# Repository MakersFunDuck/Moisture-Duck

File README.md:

# Moisture-Duck
ATtiny13A Resistive Soil Sensor for Duck Lovers

Moisture-Duck helps you keep track of your plants' soil moisture and alerts you if they need watering. It utilizes the resistance measurement technique to gauge soil moisture levels. Two probes, in combination with the substrate, constitute a variable resistor. Greater soil moisture translates to improved conductivity and decreased electrical resistance. With the addition of a 12k fixed resistor, the system creates a voltage divider. The microcontroller's ADC measures this voltage. The design is inspired by the SparkFun Soil Moisture Sensor.

Description:
------------
The Moisture Duck is a device that measures soil moisture and emits an acoustic and optical signal if the soil is too dry. The device is based on ATtiny13, which spends most of its time in sleep mode and wakes up every eight seconds to take measurements. It can also be activated by pressing the TEST button, and the correct threshold value can be set by turning the potentiometer. To calibrate the device, it should be placed in dry soil and the potentiometer should be adjusted until the alarm is triggered. The device is compiled using MicroCore and default settings should be left unchanged. Arduino core functions and libraries are not used, and the makefile can be used for compilation without Arduino IDE. The fuse settings are -U lfuse:w:0x3b:m -U hfuse:w:0xff:m.

Compiling and Uploading:
------------

You can program the ATtiny either before soldering using an SOP adapter, or after soldering using ICSP pins. The AVR Programmer Adapter can help with this.
If using the Arduino IDE

    Make sure you have installed MicroCore.
    Go to Tools -> Board -> MicroCore and select ATtiny13.
    Go to Tools and choose the following board options:
        Clock: 128 kHz internal osc.
        BOD: BOD disabled
        Timing: Micros disabled
    Connect your programmer to your PC and to the ATtiny.
    Go to Tools -> Programmer and select your ISP programmer (e.g. USBasp).
    Go to Tools -> Burn Bootloader to burn the fuses.
    Open main.ino and click Upload.

If using the precompiled hex-file

    Make sure you have installed avrdude.
    Connect your programmer to your PC and to the ATtiny.
    Open a terminal.
    Navigate to the folder with the hex-file.
    Execute the following command (if necessary replace "usbasp" with the programmer you use):

    avrdude -c usbasp -p t13 -U lfuse:w:0x3b:m -U hfuse:w:0xff:m -U flash:w:main.hex

If using the makefile (Linux/Mac)

    Make sure you have installed avr-gcc toolchain and avrdude.
    Connect your programmer to your PC and to the ATtiny.
    Open a terminal.
    Navigate to the folder with the makefile and sketch.
    Run PROGRMR=usbasp make install to compile, burn the fuses and upload the firmware (change PROGRMR accordingly).

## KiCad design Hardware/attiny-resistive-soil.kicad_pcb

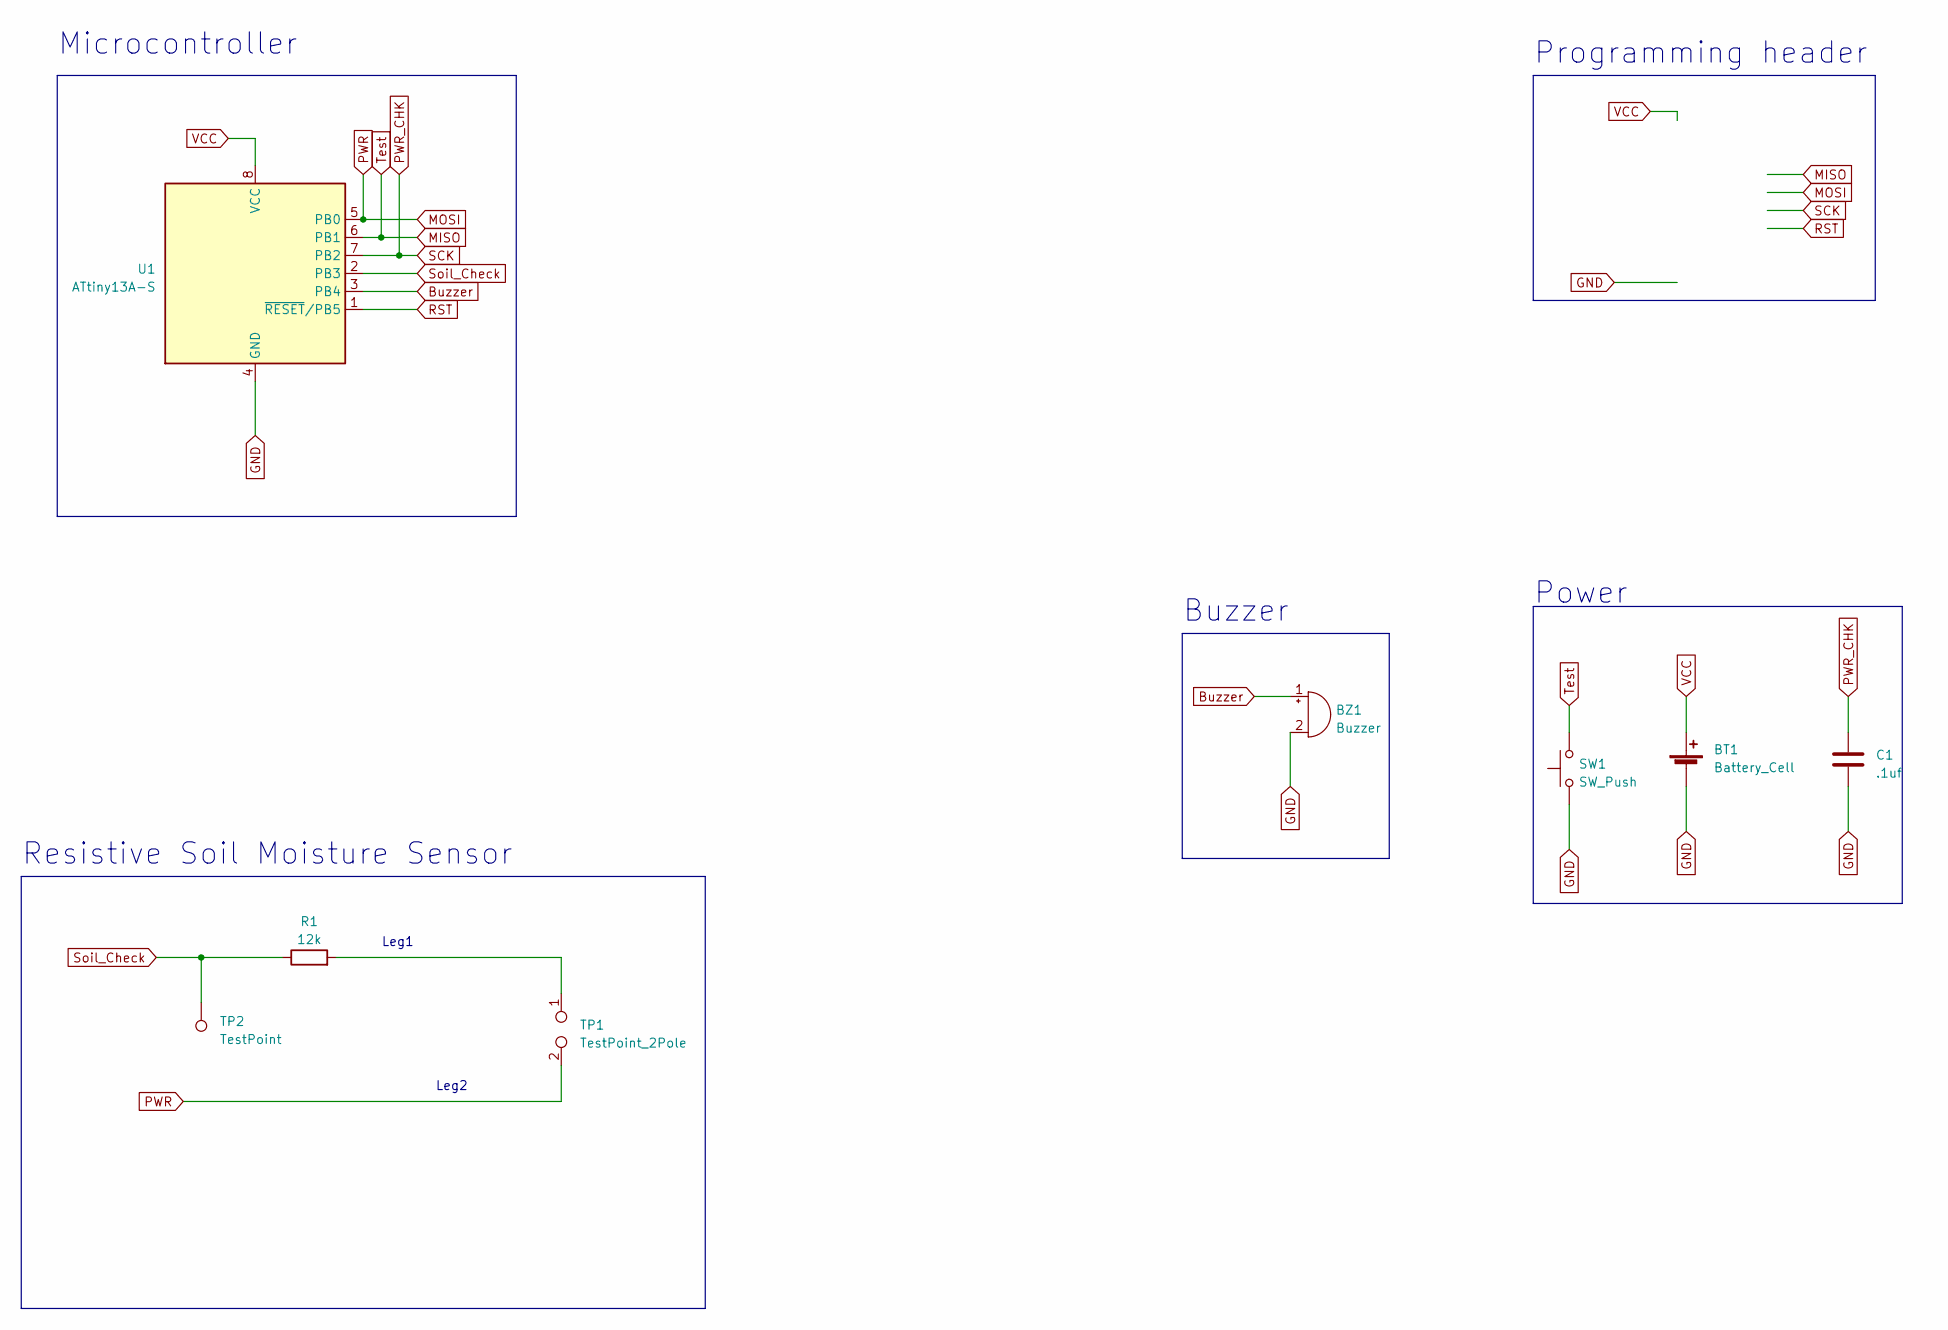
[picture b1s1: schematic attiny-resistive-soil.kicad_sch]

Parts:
BT1: Battery_Cell; BatteryHolder_Keystone_1060_1x2032
BZ1: Buzzer; MagneticBuzzer_CUI_CMT-8504-100-SMT
C1: .1uf; C_0805_2012Metric_Pad1.18x1.45mm_HandSolder
R1: 12k; R_0805_2012Metric_Pad1.20x1.40mm_HandSolder
SW1: SW_Push; SW_SPST_CK_RS282G05A3
TP1: TestPoint_2Pole; PinSocket_1x02_P2.54mm_Vertical
TP2: TestPoint; Pin_D1.4mm_L8.5mm_W2.8mm_FlatFork
U1: ATtiny13A-S; SOIC-8W_5.3x5.3mm_P1.27mm

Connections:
Buzzer: BZ1.1 (-), U1.3 (PB4)
GND: BT1.2 (-), BZ1.2 (+), C1.2, SW1.1, U1.4 (GND)
MISO: SW1.2, U1.6 (PB1)
MOSI: TP1.2, U1.5 (PB0)
unnamed: R1.2, TP1.1
PWR_CHK: C1.1, U1.7 (PB2)
RST: U1.1 (~RESET/PB5)
Soil_Check: R1.1, TP2.1, U1.2 (PB3)
VCC: BT1.1 (+), U1.8 (VCC)

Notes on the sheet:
Buzzer
Resistive Soil Moisture Sensor
Leg1
Programming header
Leg2
Microcontroller
Power

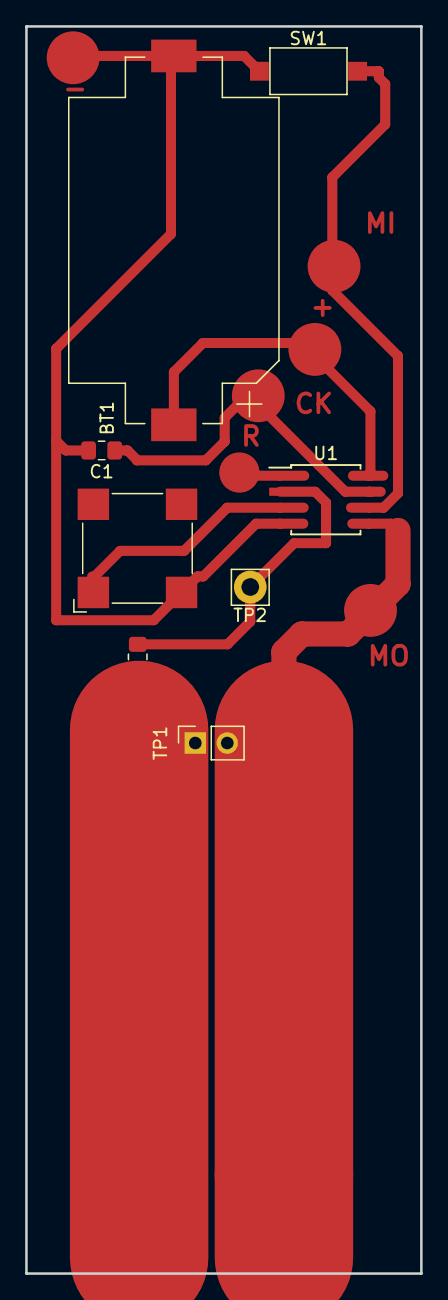
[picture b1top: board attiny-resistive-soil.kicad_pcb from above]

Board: 2 copper layers, 31.4 x 99.1 mm, 8 parts (0 on the bottom side), 8 nets.

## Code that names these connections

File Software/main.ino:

// ===================================================================================
// Project:   Moisture-Duck - Soil Moisture Monitor based on ATtiny13A
// Version:   v1.0
// Year:      2023
// Github:    https://github.com/MakersFunDuck
// Youtube:   https://www.youtube.com/@makersfunduck
// License:   GNU General Public License v3.0
// ===================================================================================
//
// Description:
// ------------
// The ATtiny13 is programmed to enter sleep mode for most of the time.
// It utilizes the watchdog timer to wake up every 2 minutes and measure soil moisture,
// comparing it to a preset threshold value.
// If the soil is too dry, it triggers a brief acoustic signal from the buzzer before going back to sleep mode.
//
// Additionally, the Moisture-Duck can also be activated by pressing the TEST button. (pin
// change interrupt).  It outputs an acoustic signal to indicate if the battery power is sufficient,
// followed by measurements of soil moisture until the button is released.

//
// To calibrate the Moisture-Duck, it should be placed in slightly dry soil,
// Then voltage 
//
// Wiring:
// -------
//                                +-\/-+
//   		   --- RST ADC0 PB5  1|°   |8  Vcc
//  Soil_Check ------- ADC3 PB3  2|    |7  PB2 ADC1 -------- PWR_CHK
// 	BUZZER ----------- ADC2 PB4  3|    |6  PB1 AIN1 OC0B --- TEST
//                          GND  4|    |5  PB0 AIN0 OC0A --- PWR
//                                +----+
//
// Compilation Settings:
// ---------------------
// Controller:  ATtiny13A
// Core:        MicroCore (https://github.com/MCUdude/MicroCore)
// Clockspeed:  128 kHz internal
// BOD:         BOD disabled
// Timing:      Micros disabled
//
// You can keep the other default settings as they are.  Don't forget to "Burn bootloader"!
// before proceeding.
// There are no Arduino core functions or libraries incorporated in this project. 
// You can use the makefile for compiling without the Arduino IDE.
// To program without Arduino IDE Fuse settings are: -U lfuse:w:0x3b:m -U hfuse:w:0xff:m



// ===================================================================================
// Libraries and Definitions
// ===================================================================================

// Libraries
#include <avr/io.h>             // for gpio
#include <avr/sleep.h>          // for the sleep modes
#include <avr/interrupt.h>      // for the interrupts
#include <avr/wdt.h>            // for the watch dog timer
#include <util/delay.h>         // for delays




// Pin definitions
#define PWR_PIN  PB0        // power pin output
#define BUZZER_PIN  PB4       // buzzer pin output
#define TEST_PIN  PB1       // test button input
#define SOIL_PIN  PB3       // Soil  pin input
#define PWR_CHK  PB2        // battery check input

// ADC port definitions
#define Soil_Check  3               // ADC port of measurement
#define VCC_Check  2        // ADC port of measurement

uint8_t count = 0;          //Watchdog counter
#define V_REF 1100          // internal reference voltage in mV

//Functions
void resetWatchdog(void);
void sleep(void);
uint8_t get_vcc(void);
void beep(int num_times);
uint16_t readADC(uint8_t port);
void delay_ms(uint16_t ms);

uint8_t vcccount = 0; //VCC measurement count


// ===================================================================================
// Watchdog and Sleep Implementation
// ===================================================================================



// Reset watchdog timer
void resetWatchdog(void) {
  cli();                                  // timed sequence coming up
  wdt_reset();                            // reset watchdog
  MCUSR = 0;                              // clear various "reset" flags
  WDTCR = (1<<WDCE)|(1<<WDE)|(1<<WDTIF);  // allow changes, disable reset
  WDTCR = (1<<WDTIE)|(1<<WDP3)|(1<<WDP0); // set WDT interval 8 seconds
  sei();                                  // interrupts are required now
      
  
}

// Go to sleep in order to save energy, wake up by watchdog timer or pin change interrupt
void sleep(void) {
  GIFR |= (1<<PCIF);                      // clear any outstanding interrupts
  resetWatchdog();                        // get watchdog ready
  sleep_mode();                           // sleep
}





// ===================================================================================
// Additional Functions
// ===================================================================================

void beep(int num_times) {
  for (int i = 0; i < num_times; i++) {
    for (int j = 0; j < 80; j++) {
      PORTB |= (1 << BUZZER_PIN);  // turn on the buzzer
      _delay_us(100);              // wait for 100 ms
      PORTB &= ~(1 << BUZZER_PIN); // turn off the buzzer
      _delay_us(100);              // wait for 100 ms
      }
    _delay_ms(100);
  }
}


// Analog read ADC
uint16_t readADC(uint8_t port) {
  ADMUX   = (port & 0x03);                // set port against Vcc
  ADCSRA |= (1<<ADSC);                    // start ADC conversion
  while(ADCSRA & (1<<ADSC));              // wait for ADC conversion complete
  return(ADC);                            // read and return measurement
}

// Analog read VCC 
//0,1uF capacitor first will be charged, and soil check pin ADC value will be read
uint16_t readVCC() {
   DDRB |= (1 << PWR_CHK);         // Set PWR_CHK as output
   PORTB |= (1 << PWR_CHK);       // Set PWR_CHK high
   _delay_ms(50);              // Wait for charging
   //DDRB |= ~(1 << PWR_CHK);   // Set PWR_CHK as input
  return readADC(VCC_Check);
  //PORTB &= ~(1 << PWR_CHK);  // Set PWR_CHK low
  //DDRB |= ~(1 << PWR_CHK);   // Set PWR_CHK as input
  
}


// Timer/Counter0 Compare Match A interrupt handler
ISR(TIM0_COMPA_vect)
{
  // Decrement timer value
  OCR0A--;
}
// Watchdog interrupt service routine
ISR(WDT_vect) {
  wdt_disable();                          // disable watchdog
  if (count > 15) // if interrupted 15. times ( after 15*8sec = 120s = 2min )
    {
      count = 0;      
    }
  else{
    count++;
    sleep();
    }
}



// ===================================================================================
// Main Function
// ===================================================================================

int main(void) {
  
  // Reset watchdog timer
  resetWatchdog();                        // do this first in case WDT fires

  // Disable unused peripherals and set sleep mode to save power
  ACSR   = (1<<ACD);                      // disable analog comparator
  DIDR0 |= (1<<SOIL_PIN )|(1<<PWR_CHK);   // disable digital input buffer on ADC pins

  // Setup pins
  DDRB  = (1<<BUZZER_PIN)|(1<<PWR_PIN);       // set output pins
  PORTB = (1<<TEST_PIN);                  // set pull-ups

  set_sleep_mode(SLEEP_MODE_PWR_DOWN);    // set sleep mode to power down

  // Setup pin change interrupt
  GIMSK = (1<<PCIE);                      // pin change interrupts enable
  PCMSK = (1<<TEST_PIN);                  // set pins for pin change interrupt
  sei();                  // enable global interrupts
       
                                
  
  
  // Loop
  while(1) {
    
    if(~PINB & (1<<TEST_PIN))   beep(1);        // alarm if test button is pressed
    ADCSRA |=  (1<<ADEN);               // enable ADC
    //if (vcccount < 15) vcccount = vcccount++;     // don't always read the vcc  to save energy
    //if (vcccount > 15){
        //uint16_t vcc = readVCC(); 
        //if (vcc<1768) beep(8);            //battery low alarm
        
    /*  
    
    Voltage = ADC_value * Vref / 1024
    = 1768 * 1.1V / 1024
    = 1,89V
    */        
     // vcccount = 0;
     // }
          
     PORTB  |=  (1<<PWR_PIN);          // power measurement circuit
     _delay_us(125);              // give it all a little time  
    do {
      if((readADC(Soil_Check)) < 512   )beep(2);  // beep twice if dry soil
    } while(~PINB & (1<<TEST_PIN));         // repeat if test button is hold
      
    /*
    
    Voltage = ADC_value * Vref / 1024
    = 512 * 1.1V / 1024
    = 0.55V
    */
    
    PORTB  &= ~(1<<PWR_PIN)|~(1<<SOIL_PIN);         // power off to prevent corrosion   
    ADCSRA &= ~(1<<ADEN);         // disable ADC
    sleep();                // sleep for a while ...
  }
}
